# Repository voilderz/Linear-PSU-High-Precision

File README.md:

# Linear-PSU-High-Precision

This project is an industrial-grade power module designed for high-stability electronic systems requiring precision voltage regulation. The design focuses on ultra-low noise energy delivery, thermal stability, and electrical safety.

---

### Changelog - v1.1 (February 2026)

* **Safety Seal:** Integrated **B72314S2271K101** MOV to the mains input for enhanced surge and transient protection.
* **Isolation Discipline:** Established a complete physical isolation barrier between AC and DC zones to eliminate arcing risks.
* **Visual Identity:** Branded the PCB with **VOI** logo and v1.1 versioning on the silkscreen layer for professional traceability.

---

## Overview
This module converts $230\text{V}$ AC grid voltage into highly regulated, low-ripple $5\text{V}$ and $15\text{V}$ DC outputs. It is engineered to serve as a reliable power platform for sensitive sensor networks and control units.

## Technical Specifications
| Parameter | Value |
| :--- | :--- |
| **Input Voltage** | $230\text{V}$ AC ($50\text{/60Hz}$) |
| **Output Voltage** | $5\text{V}$ DC Regulated |
| **Continuous Current** | $1.916\text{ A}$ Max |
| **Precision** | $0.1\%$ Tolerance (Voltage Reference Rail) |
| **Efficiency** | Up to $95\%$ (Traco Power Integration) |

## Key Engineering Features
* **High-Voltage Isolation:** A **$2.0\text{ mm}$ clearance** is maintained between primary (AC) and secondary (DC) stages, fully compliant with **IPC-2221** safety standards.
* **Thermal Management:** Power traces are widened to **$1.5\text{ mm}$ ($35\mu\text{m}$ copper)** and reinforced with "Teardrops" at pad junctions to ensure mechanical and thermal integrity under high current loads.
* **Precision Components:** Implementation of **YR1B1K0CC** series $0.1\%$ tolerance metal film resistors to minimize thermal drift and maintain long-term voltage accuracy.
* **EMI Shielding:** Integrated **Copper Pours** (Ground Planes) across all layers to suppress electromagnetic interference and ensure signal integrity.

## Bill of Materials (BOM)
| Reference | Component | MPN | Impact |
| :--- | :--- | :--- | :--- |
| **U1** | Regulator | TSR 3-2450 | High-efficiency switching regulation. |
| **TR1** | Transformer | ASL171112 | Certified primary-side galvanic isolation. |
| **R1** | Precision Resistor | MFR-25FTE52-1K | $0.1\%$ stability for feedback loops. |
| **C1** | Capacitor | B41858C5688M000 | 6800uF Low-ESR ripple suppression. |

> For the comprehensive industrial-grade BOM, see: [/BOM/BOM_Linear_PSU_Extended.csv](./BOM/BOM_Linear_PSU_Extended.csv)

## Project Structure
* **/Hardware:** KiCad schematic and PCB layout source files.
* **/Production:** Production-ready **Gerber** and **Drill** files (ZIP archive).
* **/Docs:** Full schematic PDF and critical component datasheets.
* **/Images:** 3D renders and technical captures.

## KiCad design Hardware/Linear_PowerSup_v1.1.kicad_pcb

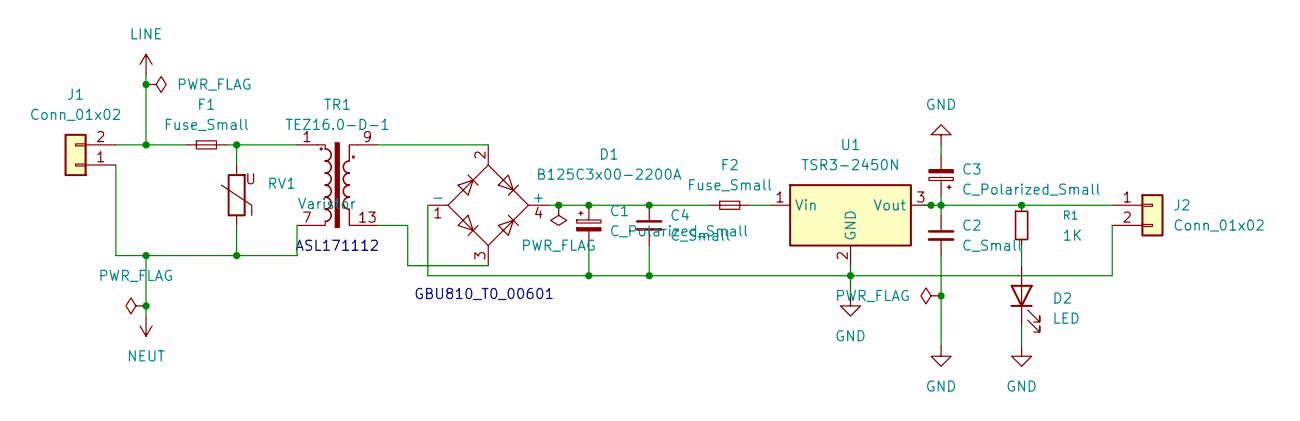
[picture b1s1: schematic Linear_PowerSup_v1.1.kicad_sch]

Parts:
C1: C_Polarized_Small; C_Radial_D18.0mm_H35.5mm_P7.50mm
C2, C4: C_Small; C_Rect_L7.2mm_W2.5mm_P5.00mm_FKS2_FKP2_MKS2_MKP2
C3: C_Polarized_Small; CP_Radial_D8.0mm_P3.50mm
D1: B125C3x00-2200A; Diode_Bridge_Vishay_GBU
D2: LED; LED_D5.0mm
F1: Fuse_Small; FUSRR508W60L835T400H810
F2: Fuse_Small; Fuse_Littelfuse_395Series
J1, J2: Conn_01x02; TerminalBlock_Phoenix_PT-1,5-2-5.0-H_1x02_P5.00mm_Horizontal
R1: 1K; RES_TYCO_YR1_TYC
RV1: Varistor; RV_Disc_D15.5mm_W5.9mm_P7.5mm
TR1: TEZ16.0-D-1; ASL171112
U1: TSR3-2450N; CONV_TSR_3-2450

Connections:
GND: C1.2, C2.2, C3.2, C4.2, D1.1 (-), D2.1 (K), J2.2, U1.2 (GND)
LINE: F1.1, J1.2
NEUT: J1.1, RV1.1, TR1.7
unnamed: C1.1, C4.1, D1.4 (+), F2.1
unnamed: D1.2, TR1.9
unnamed: D1.3, TR1.13
unnamed: D2.2 (A), R1.2
unnamed: F1.2, RV1.2, TR1.1
unnamed: C2.1, C3.1, J2.1, R1.1, U1.3 (Vout)
unnamed: F2.2, U1.1 (Vin)

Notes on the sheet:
GBU810_T0_00601
ASL171112

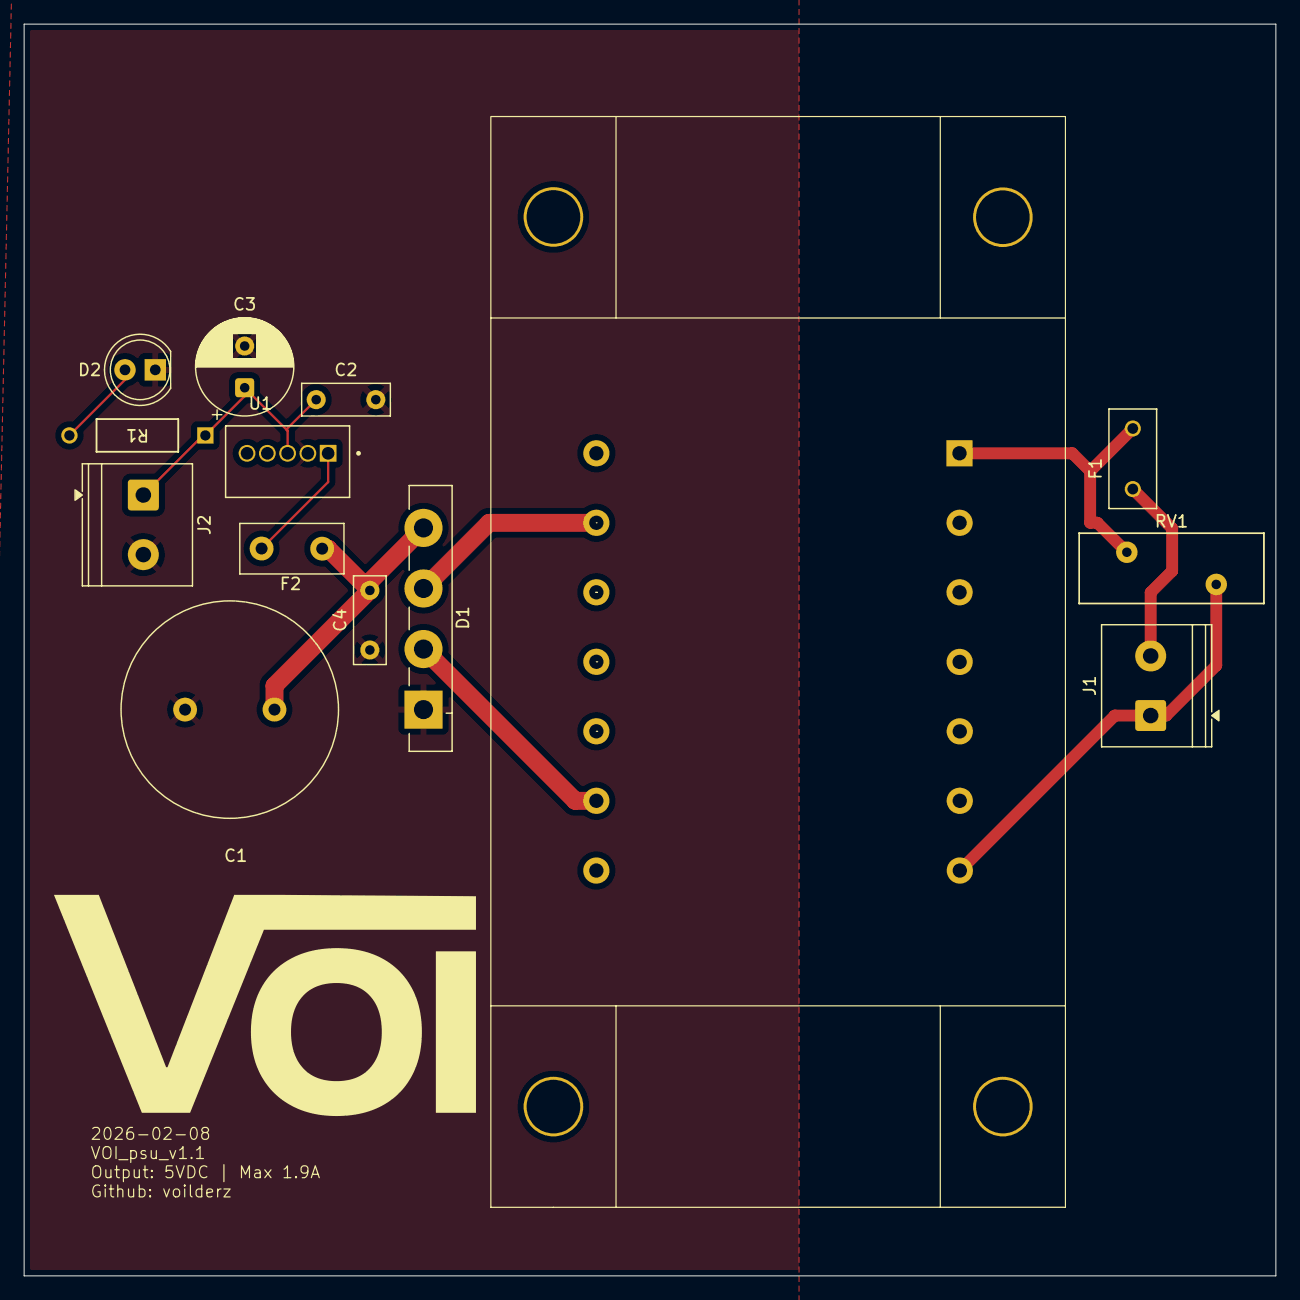
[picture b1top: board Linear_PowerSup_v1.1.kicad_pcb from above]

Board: 2 copper layers, 105.0 x 105.0 mm, 14 parts (0 on the bottom side), 10 nets.

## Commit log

2026-02-05 Enhance README with detailed project information
    Expanded project description and added technical specifications, key features, and bill of materials.
2026-02-08 v1.1 Update
2026-02-08 Update README with changelog for v1.1
    Added changelog for version 1.1 including safety improvements and branding.
2026-02-08 Added Library files to project
